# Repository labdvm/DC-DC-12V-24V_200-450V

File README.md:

# DC-DC-12V-24V_200-450V
DC-DC Boost convertor up to 70W@450V, 70W@24V
This is modified DC-DC convertor from chinese product from Aliexpress with little enhancement.
Take out the transformer from original PCB and place to this PCB !
V1.4 and V2.1
Z32IT

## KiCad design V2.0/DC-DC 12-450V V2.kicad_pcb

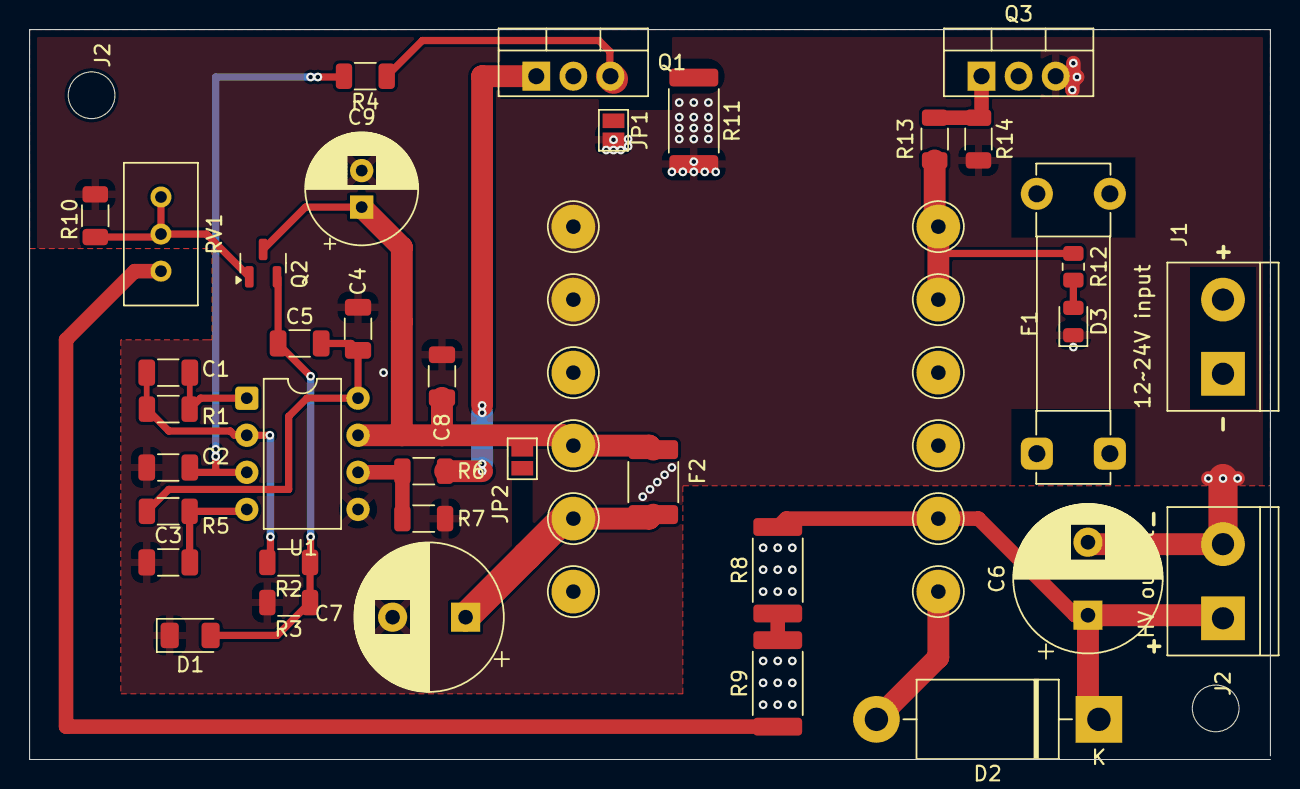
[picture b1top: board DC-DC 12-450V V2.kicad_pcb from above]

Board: 2 copper layers, 85.0 x 50.0 mm, 49 parts (0 on the bottom side), 22 nets.

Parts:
C1, C8: 100n; C_1206_3216Metric
C2, C4, C5: 10n; C_1206_3216Metric
C3: 3n3; C_1206_3216Metric
C6: 10u/450V; CP_Radial_D10.0mm_P5.00mm
C7: 1000u/35V; CP_Radial_D10.0mm_P5.00mm
C9: 100u/35V; CP_Radial_D7.5mm_P2.50mm
D1: Green; LED_1206_3216Metric
D2: UF5407-8; D_DO-201AD_P15.24mm_Horizontal
D3: Amber; LED_0805_2012Metric
F1: 8~10A; Fuseholder_Clip-5x20mm_Bel_FC-203-22_Lateral_P17.80x5.00mm_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
F2: 1.5A/24V; Fuse_1812_4532Metric_Pad1.30x3.40mm_HandSolder
J1: 12~24V input; TerminalBlock_bornier-2_P5.08mm
J2: HV output; TerminalBlock_bornier-2_P5.08mm
JP1, JP2: SolderJumper_2_Open; SolderJumper-2_P1.3mm_Open_Pad1.0x1.5mm
PAD1, PAD6, PAD7: +12V; TestPoint_THTPad_D3.0mm_Drill1.5mm
PAD2, PAD3, PAD5, PAD8, PAD10, PAD11: e; TestPoint_THTPad_D3.0mm_Drill1.5mm
PAD9, PAD9#2: TestPoint_THTPad_D3.0mm_Drill1.5mm
PAD12: Q1-D; TestPoint_THTPad_D3.0mm_Drill1.5mm
Q1, Q3: IRF3205; TO-220-3_Vertical
Q2: S8050; SOT-23
R1: 100K; R_1206_3216Metric
R2, R3: 1K; R_1206_3216Metric
R4: 150R; R_1206_3216Metric
R5, R7, R14: 5K1; R_1206_3216Metric
R6: 20R; R_1206_3216Metric
R8, R9: 240K/1W; R_2512_6332Metric
R10: 3K; R_1206_3216Metric
R11: 0.015R/3W; R_2512_6332Metric
R12: 2K2; R_0805_2012Metric
R13: 100R; R_1206_3216Metric
RV1: 5K; Potentiometer_Bourns_3296W_Vertical
U1: UC3843BN_DIP8; DIP-8_W7.62mm

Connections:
+12~24V: C7.1, F2.1, JP2.1 (A), PAD2.2, PAD7.7, PAD8.8, R12.2, R13.1
/Q1-S: JP1.1 (A), Q1.3 (S), R4.2, R11.1
/VCC: C8.1, C9.1, F2.2, JP2.2 (B), PAD3.3, Q2.3 (C), U1.7 (VCC)
GND: C2.2, C3.1, C4.2, C6.2, C7.2, C8.2, C9.2, D1.1 (K), D3.1 (K), J2.2, JP1.2 (B), Q3.3 (S), R3.2, R7.2, R10.2, R11.2, R14.2, U1.5 (GND)
unnamed: C5.1, D1.2 (A), Q2.2 (E), R2.1, R3.1
unnamed: D2.2 (A), PAD12.12
unnamed: C6.1, D2.1 (K), J2.1, PAD11.11, R8.2
unnamed: D3.2 (A), R12.1
unnamed: F1.1, J1.1
unnamed: PAD5.5, PAD6.6
unnamed: Q1.1 (G), R6.1
unnamed: Q2.1 (B), R10.1, RV1.2, RV1.3
unnamed: F1.2, Q3.2 (D)
unnamed: Q3.1 (G), R13.2, R14.1
unnamed: R8.1, R9.2
unnamed: R9.1, RV1.1
unnamed: C1.1, R1.2, U1.1 (COMP)
unnamed: C2.1, R4.1, U1.3 (CS)
unnamed: C1.2, R1.1, R2.2, U1.2 (FB)
unnamed: R6.2, R7.1, U1.6 (OUT)
unnamed: C3.2, R5.2, U1.4 (RC)
unnamed: C4.1, C5.2, R5.1, U1.8 (VREF)

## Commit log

2026-01-24 Update README with transformer placement instruction
    Added note about transformer placement on PCB.
